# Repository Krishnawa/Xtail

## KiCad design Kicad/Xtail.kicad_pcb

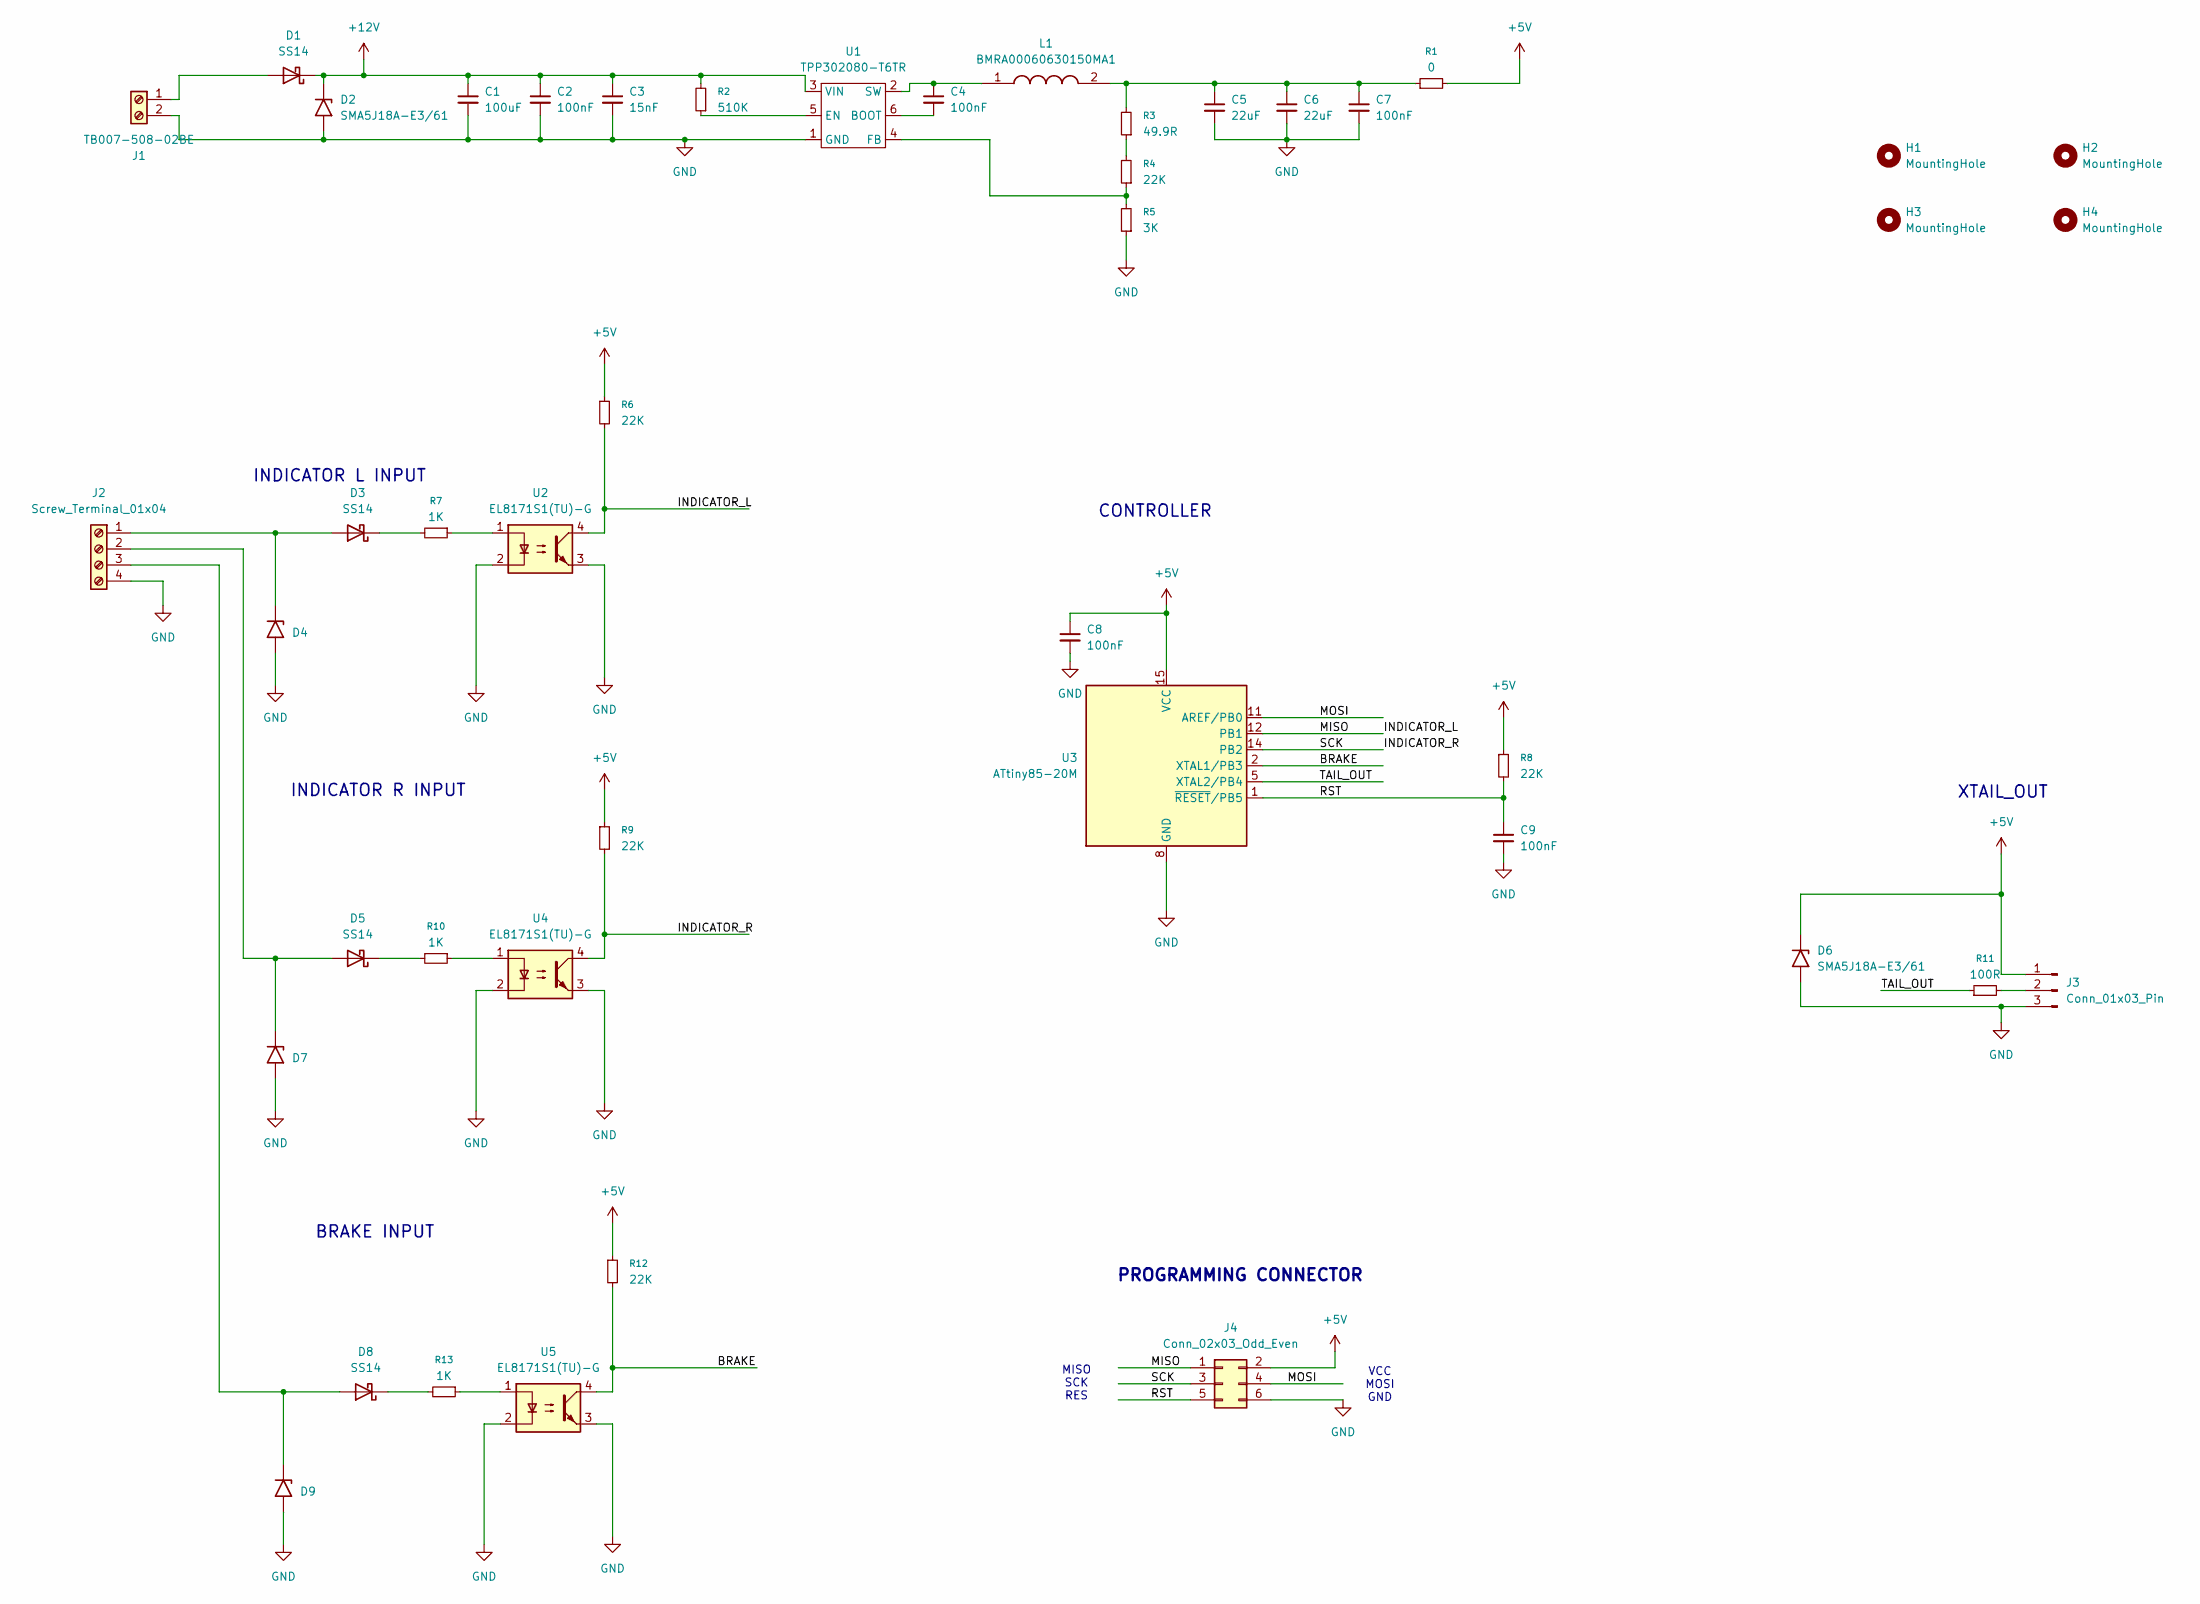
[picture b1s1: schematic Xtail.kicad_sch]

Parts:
C1: 100uF; CP_Elec_6.3x7.7; Mouser Part Number UWT1V101MCL1GS
C2, C4, C7, C8, C9: 100nF; C_0603_1608Metric_Pad1.08x0.95mm_HandSolder; Mouser Part Number CML0603X7R104KT50V
C3: 15nF; C_0603_1608Metric_Pad1.08x0.95mm_HandSolder; Mouser Part Number CGA3E2X7R1H153M080AA
C5, C6: 22uF; CP_Elec_5x3; Mouser Part Number EDH226M016S9DAA
D1, D3, D5, D8: SS14; D_SMA; Mouser Part Number SS14
D2, D4, D6, D7, D9: SMA5J18A-E3/61; D_SMA; Mouser Part Number SMA5J18A-E3/61
H1, H2, H3, H4: MountingHole; MountingHole_2mm
J1: TB007-508-02BE; TerminalBlock_CUI_TB007-508-02_1x02_P5.08mm_Horizontal; Mouser Part Number TB007-508-02BE
J2: Screw_Terminal_01x04; TerminalBlock_CUI_TB007-508-04_1x04_P5.08mm_Horizontal
J3: Conn_01x03_Pin; PinHeader_1x03_P2.54mm_Vertical
J4: Conn_02x03_Odd_Even; PinHeader_2x03_P2.54mm_Vertical
L1: BMRA00060630150MA1; L_APV_APH0620; Mouser Part Number SDCL1V3015-150M-R
R1: 0; R_0805_2012Metric_Pad1.20x1.40mm_HandSolder; Mouser Part Number RCS08050000Z0EA
R2: 510K; R_0603_1608Metric_Pad0.98x0.95mm_HandSolder; Mouser Part Number RC0603FR-07510KL
R3: 49.9R; R_0603_1608Metric_Pad0.98x0.95mm_HandSolder; Mouser Part Number MCT06030C4999FP500
R4, R6, R8, R9, R12: 22K; R_0603_1608Metric_Pad0.98x0.95mm_HandSolder; Mouser Part Number CR0603-FX-2202ELF
R5: 3K; R_0603_1608Metric_Pad0.98x0.95mm_HandSolder; Mouser Part Number ERJ-3EKF3001V
R7, R10, R13: 1K; R_0805_2012Metric_Pad1.20x1.40mm_HandSolder; Mouser Part Number RK73H2ATTDD1001F
R11: 100R; R_0603_1608Metric_Pad0.98x0.95mm_HandSolder; Mouser Part Number CRT0603-DY-1000ELF
U1: TPP302080-T6TR; SOT-23-6_Handsoldering; Mouser Part Number TPP302080-T6TR
U2, U4, U5: EL8171S1(TU)-G; DIP-4_W8.89mm_SMDSocket_LongPads; Mouser Part Number EL8171S1(TU)-G
U3: ATtiny85-20M; QFN-20-1EP_4x4mm_P0.5mm_EP2.6x2.6mm

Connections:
+5V: C8.1, D6.1 (A1), J3.1, J4.2, R1.2, R6.1, R8.1, R9.1, R12.1, U3.15 (VCC)
+12V: C1.1, C2.1, C3.1, D1.1 (K), D2.1 (A1), R2.2, U1.3 (VIN)
/BRAKE: R12.2, U3.2 (XTAL1/PB3), U5.4
/INDICATOR_L: J4.1, R6.2, U2.4, U3.12 (PB1)
/INDICATOR_R: J4.3, R9.2, U3.14 (PB2), U4.4
/MOSI: J4.4, U3.11 (AREF/PB0)
/RST: C9.1, J4.5, R8.2, U3.1 (~RESET/PB5)
/TAIL_OUT: R11.1, U3.5 (XTAL2/PB4)
GND: C1.2, C2.2, C3.2, C5.2, C6.2, C7.2, C8.2, C9.2, D2.2 (A2), D4.2 (A2), D6.2 (A2), D7.2 (A2), D9.2 (A2), J1.2, J2.4, J3.3, J4.6, R5.1, U1.1 (GND), U2.2, U2.3, U3.8 (GND), U3.21 (GND), U4.2, U4.3, U5.2, U5.3
unnamed: C5.1, C6.1, C7.1, L1.2, R1.1, R3.2
unnamed: D1.2 (A), J1.1
unnamed: D3.2 (A), D4.1 (A1), J2.1
unnamed: D3.1 (K), R7.2
unnamed: D5.2 (A), D7.1 (A1), J2.2
unnamed: D5.1 (K), R10.2
unnamed: D8.2 (A), D9.1 (A1), J2.3
unnamed: D8.1 (K), R13.2
unnamed: J3.2, R11.2
unnamed: R3.1, R4.2
unnamed: R7.1, U2.1
unnamed: R10.1, U4.1
unnamed: R13.1, U5.1
unnamed: C4.2, U1.6 (BOOT)
unnamed: R2.1, U1.5 (EN)
unnamed: R4.1, R5.2, U1.4 (FB)
unnamed: C4.1, L1.1, U1.2 (SW)

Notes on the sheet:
XTAIL_OUT
VCC MOSI GND
BRAKE INPUT
PROGRAMMING CONNECTOR
INDICATOR L INPUT
CONTROLLER
MISO SCK RES
INDICATOR R INPUT

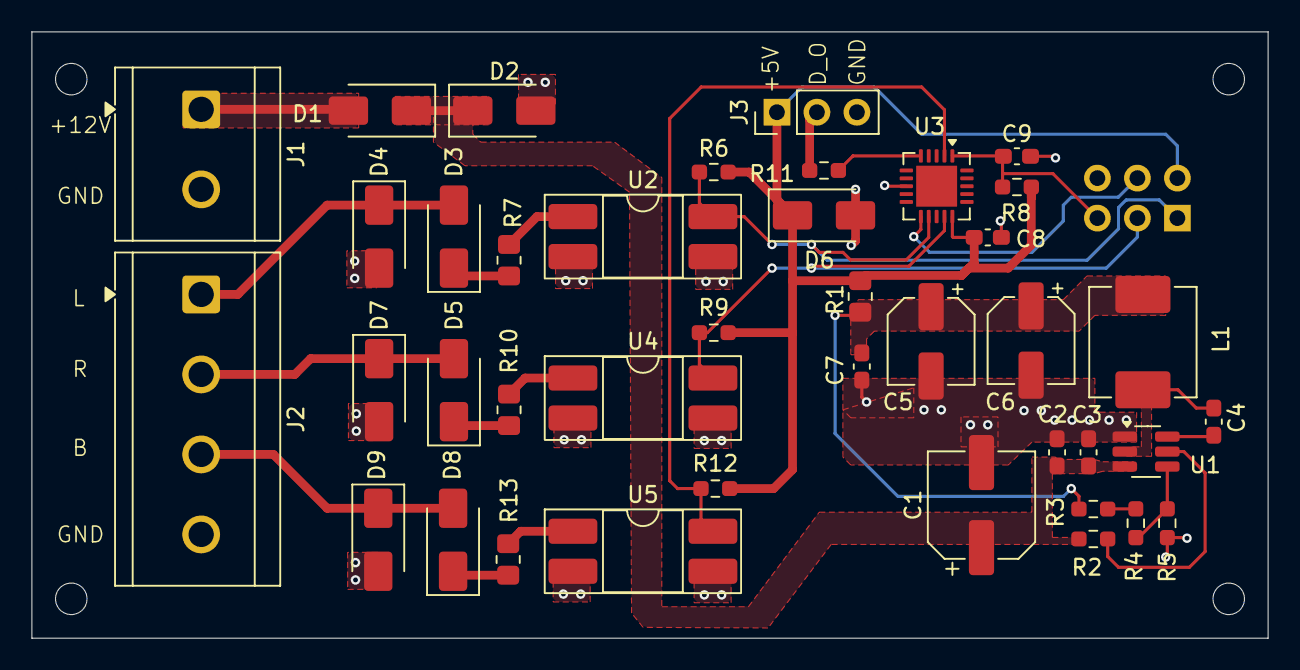
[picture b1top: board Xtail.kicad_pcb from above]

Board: 2 copper layers, 78.5 x 38.5 mm, 45 parts (1 on the bottom side), 26 nets.

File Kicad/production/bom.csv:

Designator,Footprint,Quantity,Value,LCSC Part #
C1,CP_Elec_6.3x7.7,1,100uF,
"C2, C4, C7, C8, C9",0603,5,100nF,
C3,0603,1,15nF,
"C5, C6",CP_Elec_5x3,2,22uF,
"D1, D3, D5, D8",D_SMA,4,SS14,
"D2, D4, D6, D7, D9",D_SMA,5,SMA5J18A-E3/61,
J1,TerminalBlock_CUI_TB007-508-02_1x02_P5.08mm_Horizontal,1,TB007-508-02BE,
J2,TerminalBlock_CUI_TB007-508-04_1x04_P5.08mm_Horizontal,1,Screw_Terminal_01x04,
J3,PinHeader_1x03_P2.54mm_Vertical,1,Conn_01x03_Pin,
J4,PinHeader_2x03_P2.54mm_Vertical,1,Conn_02x03_Odd_Even,
L1,L_APV_APH0620,1,BMRA00060630150MA1,
R1,0805,1,0,
"R10, R13, R7",0805,3,1K,
R11,0603,1,100R,
"R12, R4, R6, R8, R9",0603,5,22K,
R2,0603,1,510K,
R3,0603,1,49.9R,
R5,0603,1,3K,
U1,SOT-23-6_Handsoldering,1,TPP302080-T6TR,
"U2, U4, U5",DIP-4_W8.89mm_SMDSocket_LongPads,3,EL8171S1(TU)-G,
U3,QFN-20-1EP_4x4mm_P0.5mm_EP2.6x2.6mm,1,ATtiny85-20M,
